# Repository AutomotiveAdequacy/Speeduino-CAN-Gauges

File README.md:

# Speeduino-CAN-Gauges
An analog stepper motor gauge cluster that gets data over serial from a speeduino ECU

 - AX1201728SG stepper drivers and X25.168 stepper motors
 - right now setup for 5 gauges
 - warning LED's on each gauge
 - LED Alternator excite that should work with most cars that normally use a incandescent bulb as an excite
 - Arduino Nano controlled
 - two spare analog inputs if wanted to have a button to control the 7-seg display, or analog input over CAN as a sensor for a speeduino

This is all a work in process, I worked through this pretty quick so there are a few areas that need refining but hopfully getting this out there allows people to pick and choose parts for their own projects.

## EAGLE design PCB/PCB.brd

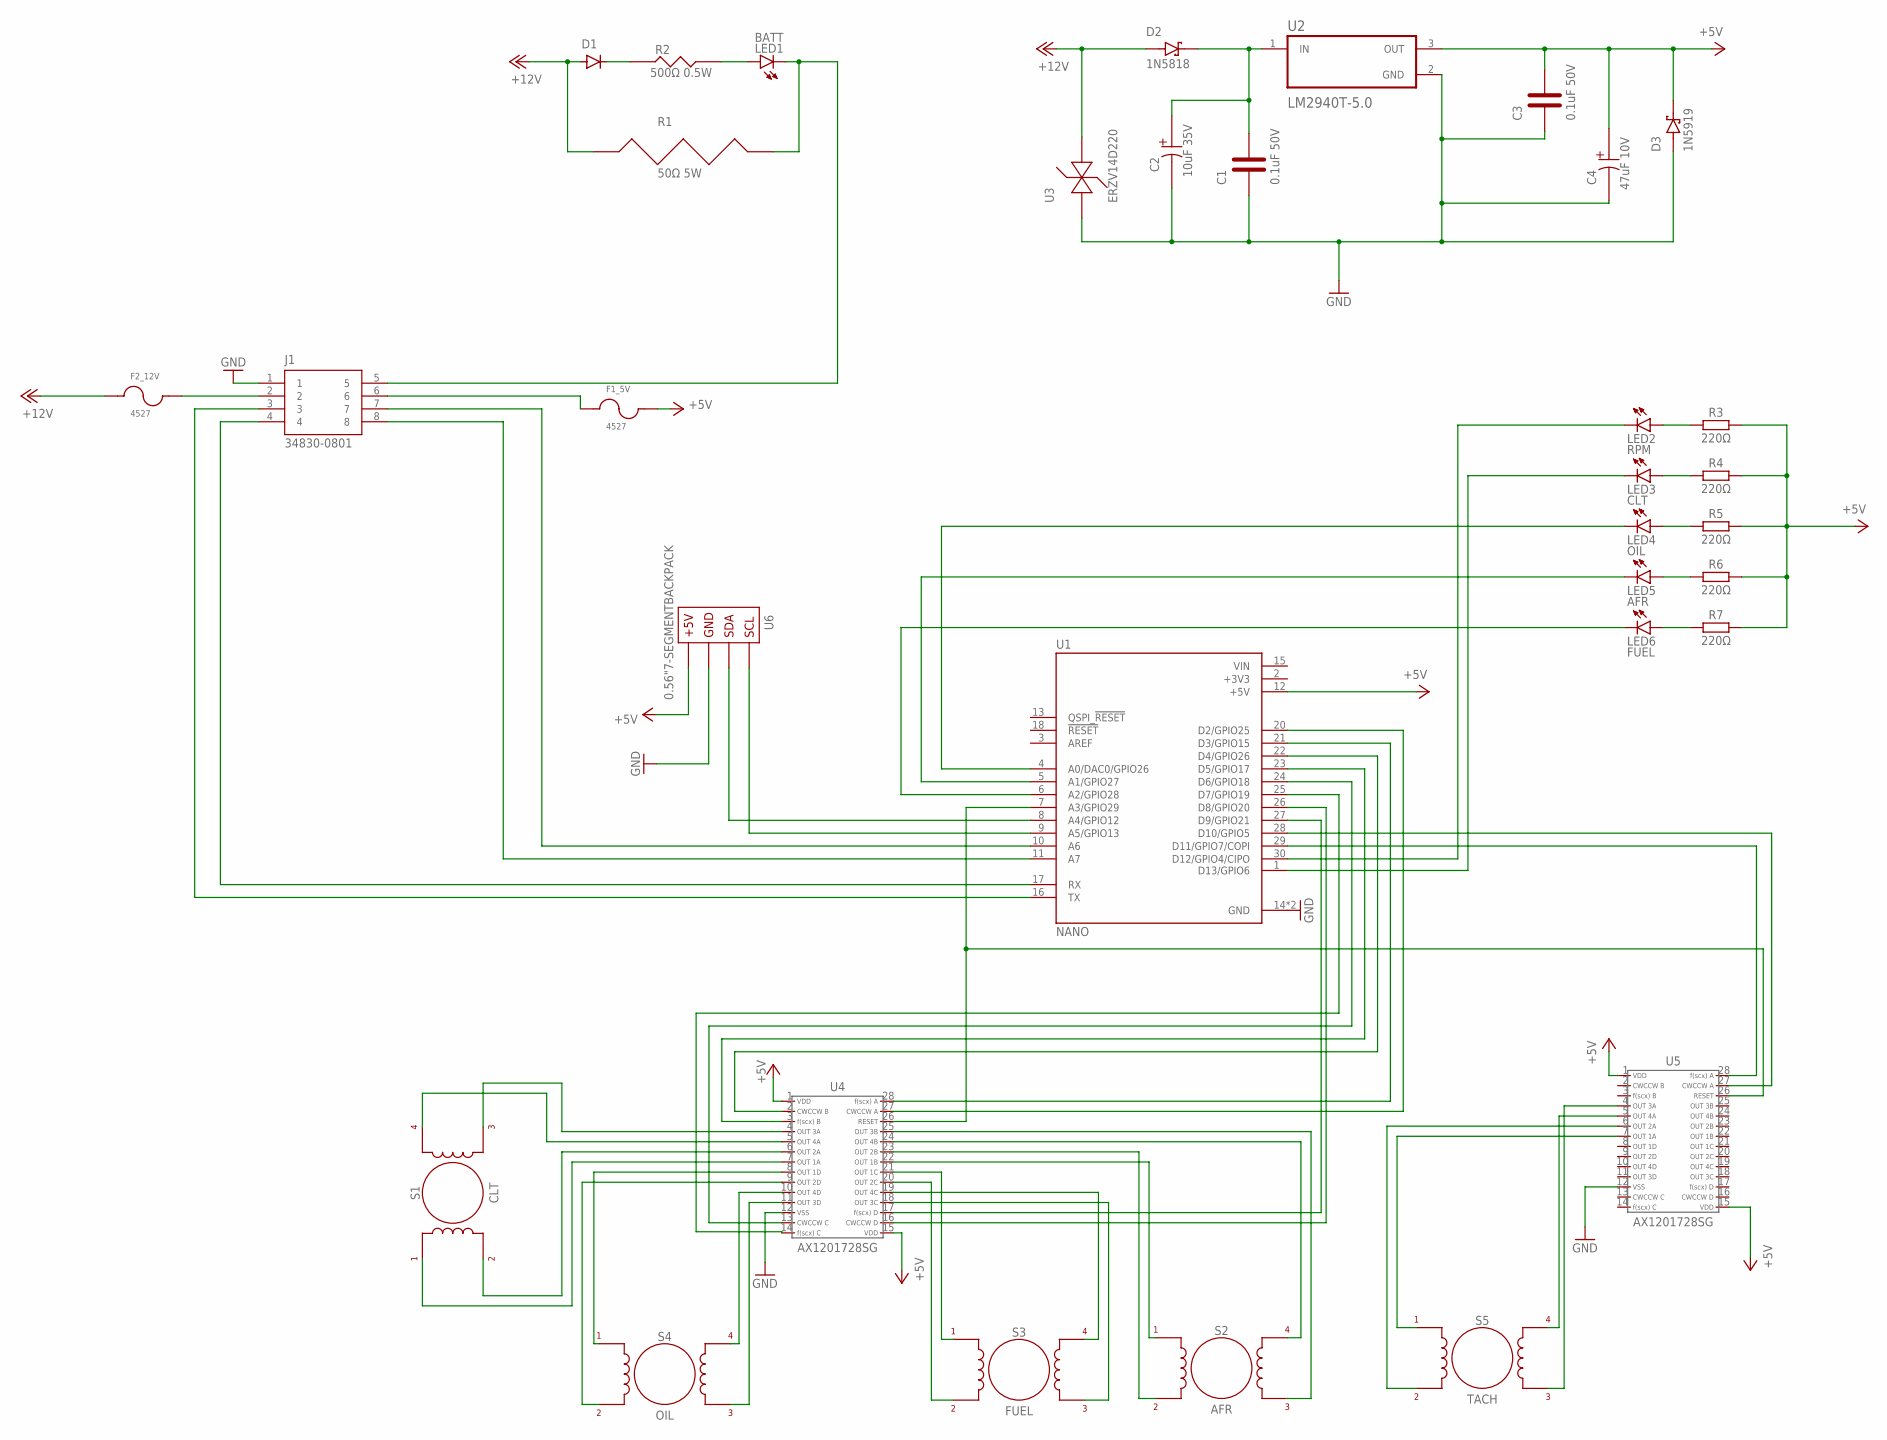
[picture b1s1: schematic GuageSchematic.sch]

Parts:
C1, C3: 0.1uF 50V; C322C104K5R5TA
C2: 10uF 35V; T356G106K035AT
C4: 47uF 10V; TAP476K006CCS
D1: 1N4004; DO-41
D2: 1N5818; DIOAD1036W78L520D271
D3: 1N5919; DIOAD1036W78L520D271
F1_5V, F2_12V: 4527
J1: 34830-0801; MOLEX_34830-0801
LED1: BATT; LED5MM
LED2: RPM; LED5MM
LED3: CLT; LED5MM
LED4: OIL; LED5MM
LED5: AFR; LED5MM
LED6: FUEL; LED5MM
R1: 50Ω 5W; 25J50RE
R2: 500Ω 0.5W; CMF55
R3, R4, R5, R6, R7: 220Ω; RESAD724W46L381D178B
S1: CLT; X27.168
S2: AFR; X27.168
S3: FUEL; X27.168
S4: OIL; X27.168
S5: TACH; X27.168
U1: NANO; MODULE_ABX00053
U2: LM2940T-5.0; TO254P1054X470X1955-3
U3: ERZV14D220
U4, U5: AX1201728SG
U6: 0.56"7-SEGMENTBACKPACK

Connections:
+3V3: U1.2 (+3V3)
+5V: C3.2, C4.1, D3.K, F1_5V.2, R3.2, R4.2, R5.2, R6.2, R7.2, U1.12 (+5V), U2.3 (OUT), U4.1, U4.15, U5.1, U5.15, U6.P$4
+12V: D1.A, D2.A, F2_12V.1, R1.1, U3.2
GND: C1.1, C2.2, C3.1, C4.2, D3.A, J1.1, U1.14 (GND), U1.19 (GND), U2.2 (GND), U3.1, U4.12, U5.12, U6.P$3
unnamed: J1.3, U1.16 (TX)
unnamed: J1.4, U1.17 (RX)
unnamed: J1.7, U1.10 (A6)
unnamed: J1.8, U1.11 (A7)
unnamed: D1.C, R2.1
unnamed: LED1.A, R2.2
unnamed: J1.5, LED1.K (C), R1.2
unnamed: C1.2, C2.1, D2.K, U2.1 (IN)
unnamed: F1_5V.1, J1.6
unnamed: F2_12V.2, J1.2
unnamed: U1.7 (A3/GPIO29), U4.26, U5.26
unnamed: U1.20 (D2/GPIO25), U4.27
unnamed: U1.21 (D3/GPIO15), U4.28
unnamed: U1.22 (D4/GPIO26), U4.2
unnamed: U1.23 (D5/GPIO17), U4.3
unnamed: U1.24 (D6/GPIO18), U4.13
unnamed: U1.25 (D7/GPIO19), U4.14
unnamed: U1.26 (D8/GPIO20), U4.16
unnamed: U1.27 (D9/GPIO21), U4.17
unnamed: U1.28 (D10/GPIO5), U5.27
unnamed: U1.29 (D11/GPIO7/COPI), U5.28
unnamed: LED2.A, R3.1
unnamed: LED3.A, R4.1
unnamed: LED4.A, R5.1
unnamed: LED5.A, R6.1
unnamed: LED6.A, R7.1
unnamed: LED2.K (C), U1.30 (D12/GPIO4/CIPO)
unnamed: LED3.K (C), U1.1 (D13/GPIO6)
unnamed: LED4.K (C), U1.4 (A0/DAC0/GPIO26)
unnamed: LED5.K (C), U1.5 (A1/GPIO27)
unnamed: LED6.K (C), U1.6 (A2/GPIO28)
unnamed: S1.P$1, U4.7
unnamed: S1.P$2, U4.6
unnamed: S1.P$3, U4.4
unnamed: S1.P$4, U4.5
unnamed: S5.P$1, U5.7
unnamed: S5.P$2, U5.6
unnamed: S5.P$3, U5.4
unnamed: S5.P$4, U5.5
unnamed: S4.P$1, U4.8
unnamed: S4.P$2, U4.9
unnamed: S4.P$3, U4.11
unnamed: S4.P$4, U4.10
unnamed: S3.P$3, U4.18
unnamed: S3.P$4, U4.19
unnamed: S3.P$2, U4.20
unnamed: S3.P$1, U4.21
unnamed: S2.P$1, U4.22
unnamed: S2.P$2, U4.23
unnamed: S2.P$4, U4.24
unnamed: S2.P$3, U4.25
unnamed: U1.8 (A4/GPIO12), U6.P$2
unnamed: U1.9 (A5/GPIO13), U6.P$1
VIN: U1.15 (VIN)

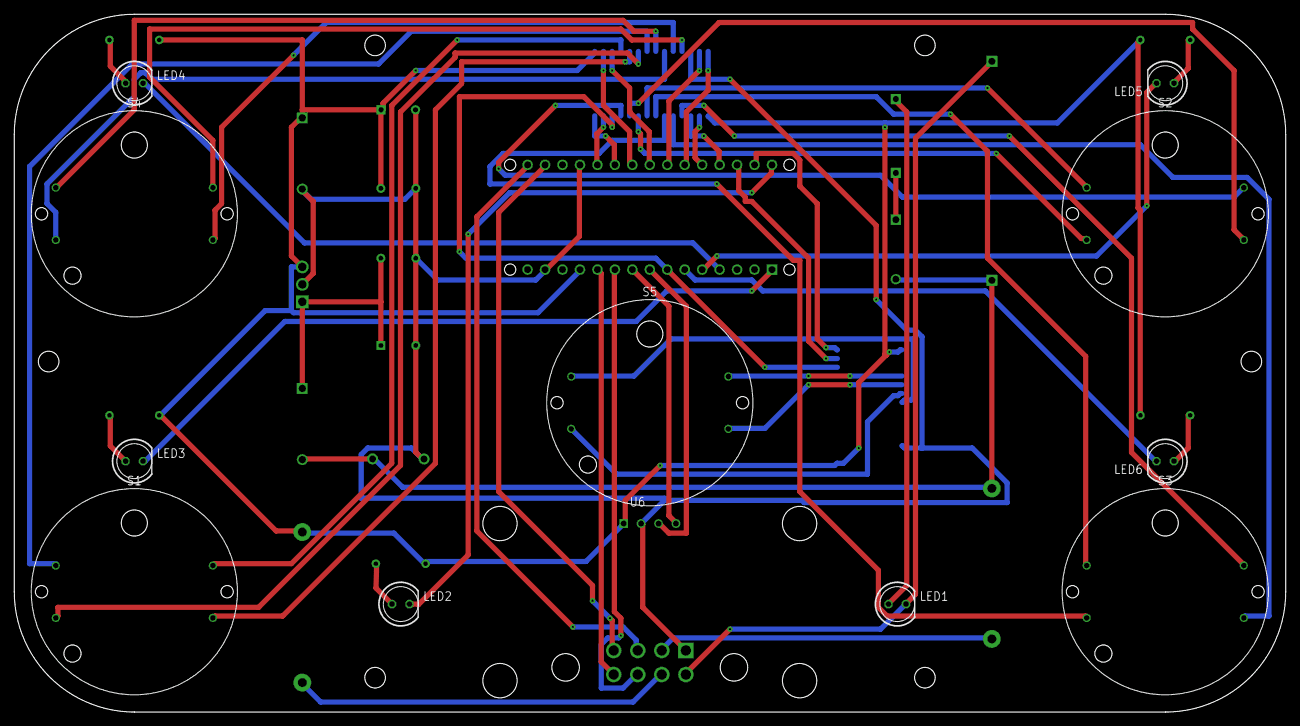
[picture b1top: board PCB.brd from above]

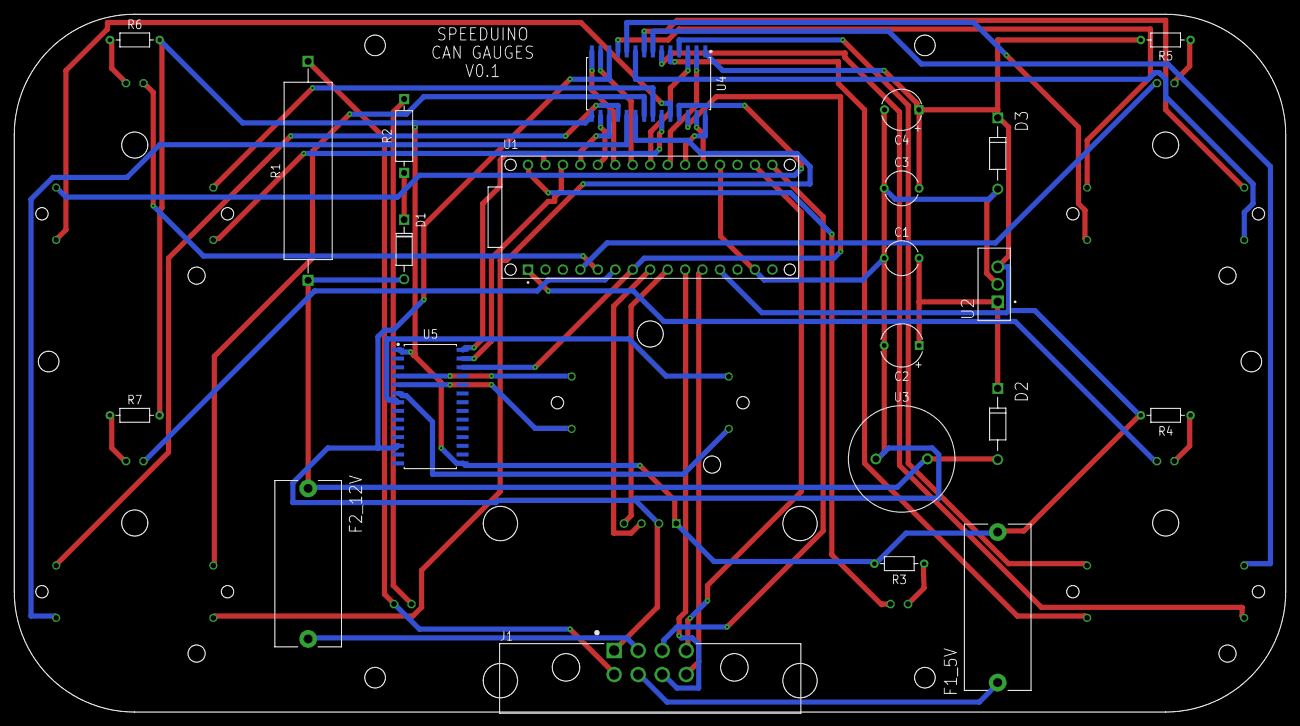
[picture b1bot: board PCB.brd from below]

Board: 2 copper layers, 185.0 x 101.5 mm, 34 parts (22 on the bottom side), 56 nets.

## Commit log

2022-02-13 Create CAD Readme
2022-02-13 Create BOM
2022-02-13 Create RE
